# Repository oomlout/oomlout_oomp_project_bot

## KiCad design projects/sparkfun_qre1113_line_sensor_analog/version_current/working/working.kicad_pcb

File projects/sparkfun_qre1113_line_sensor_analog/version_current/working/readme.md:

# QRE1113_Line_Sensor-Analog by sparkfun  
This is a harvested standardized copy of a project from github.  
The original project can be found at:  
https://github.com/sparkfun/QRE1113_Line_Sensor-Analog  
Please consult that link for additional, details, files, and license information.  
Note: It was auto harvested and if the original repo had more than one board file or anything out of the ordinary the files here are likely not representative.

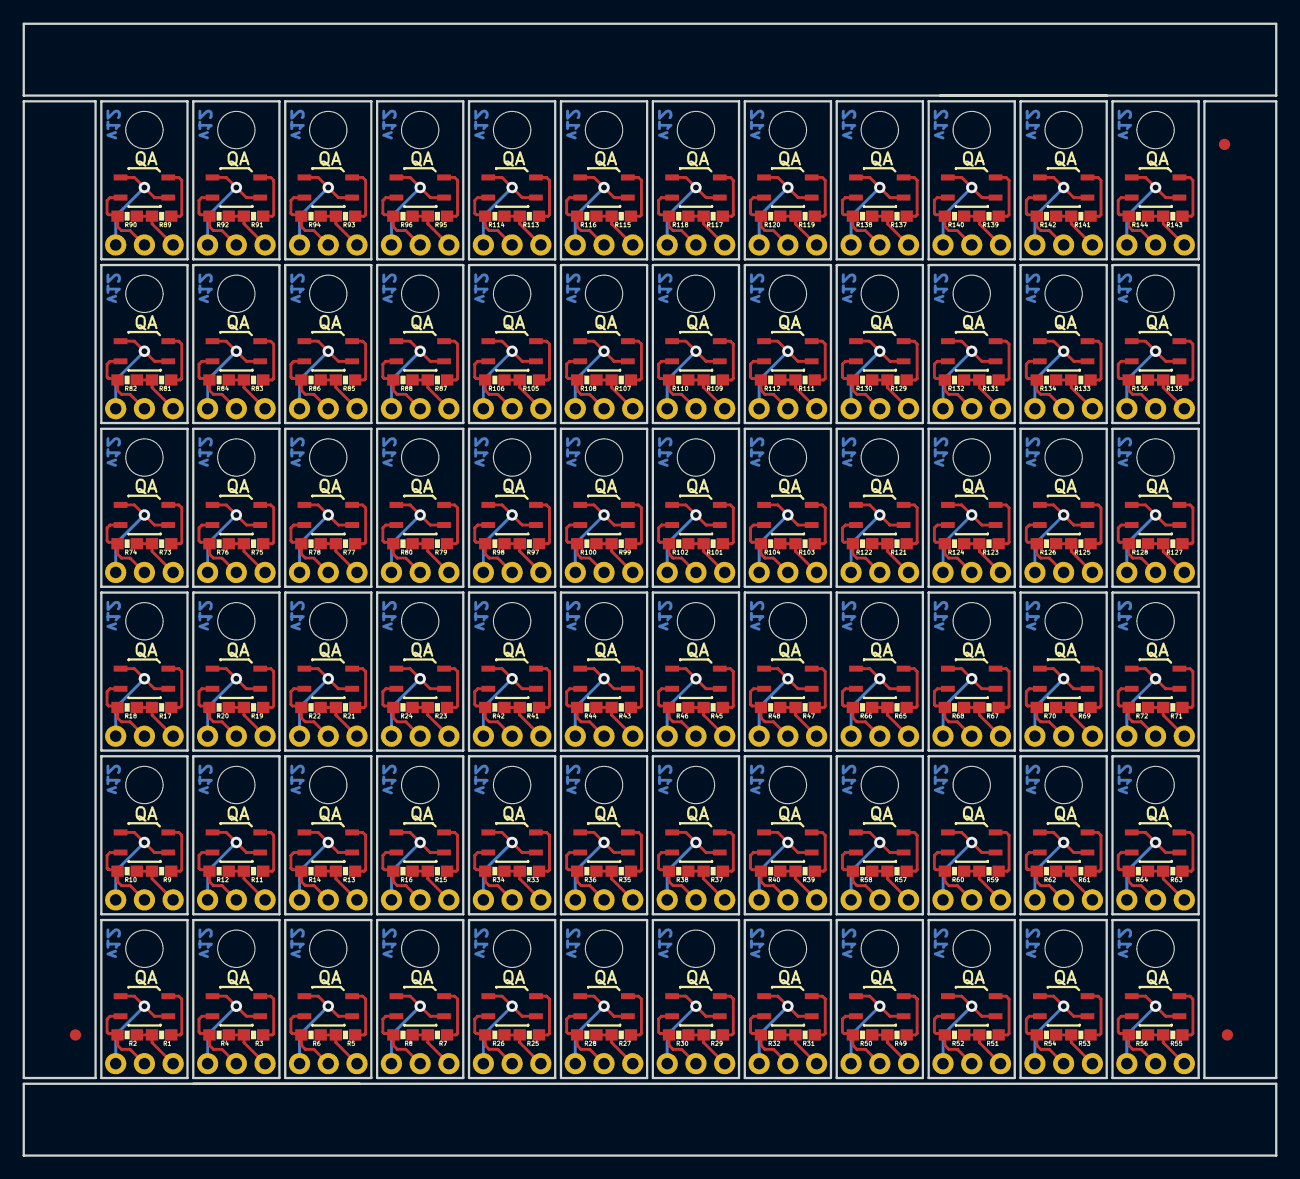
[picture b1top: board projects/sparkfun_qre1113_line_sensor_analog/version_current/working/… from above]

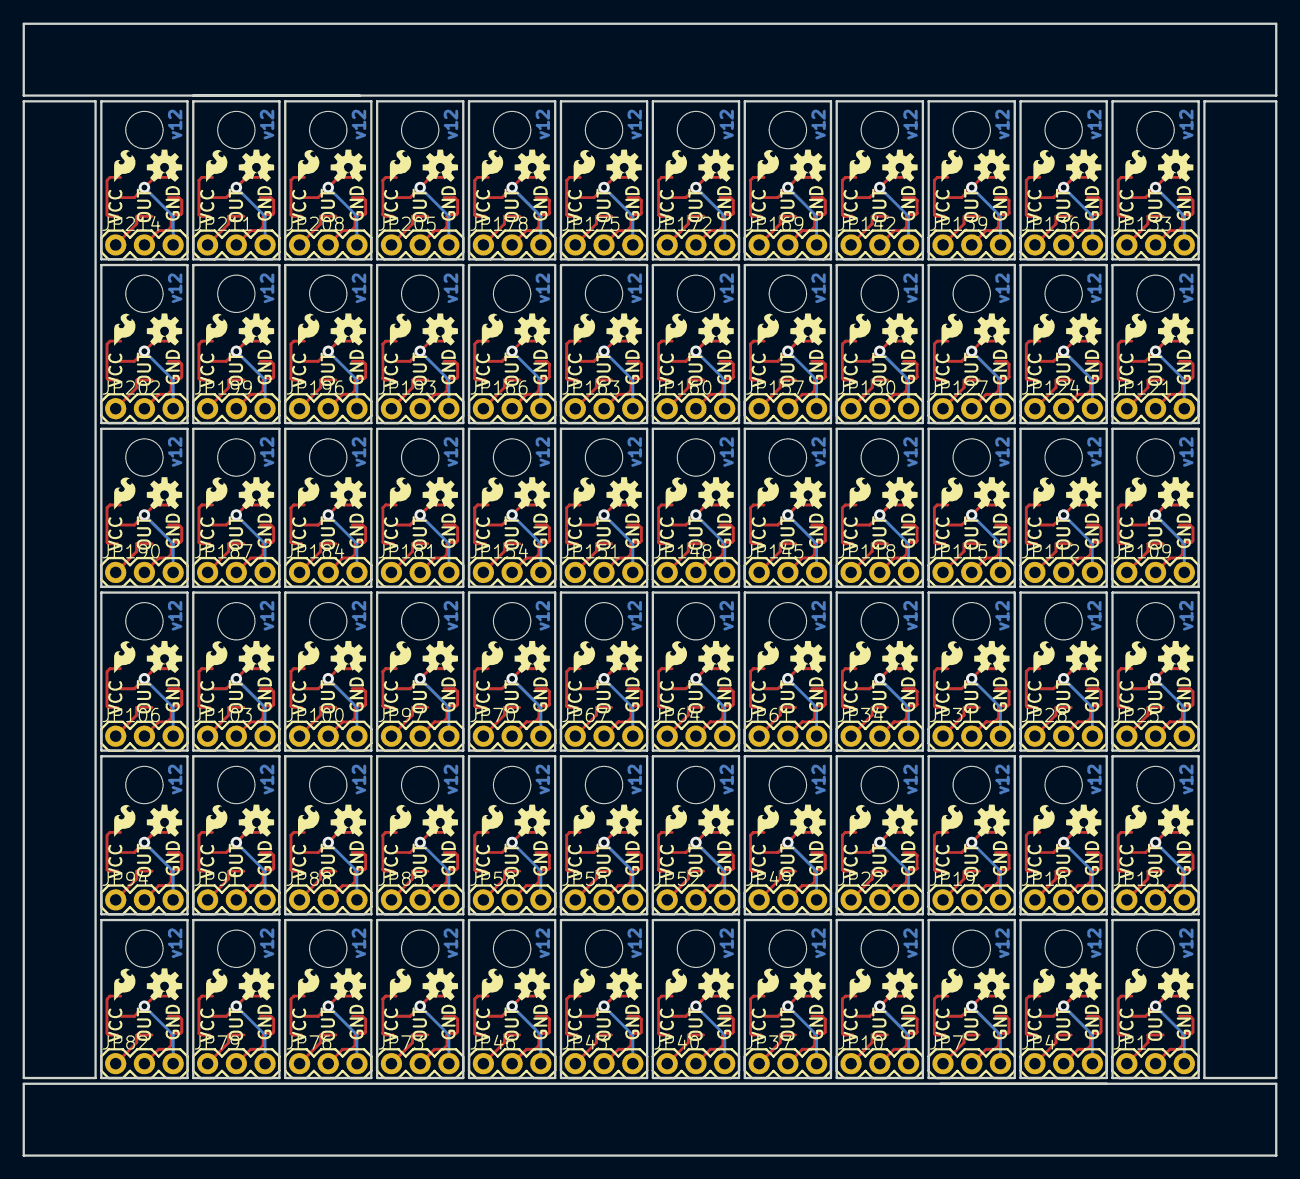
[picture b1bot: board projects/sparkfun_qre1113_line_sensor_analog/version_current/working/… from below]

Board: 2 copper layers, 110.7 x 100.1 mm, 507 parts (216 on the bottom side), 288 nets.

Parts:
E$1, E$4, E$5: FIDUCIAL-1X2
JP1, JP4, JP7, JP10, JP13, JP16, JP19, JP22, JP25, JP28, JP31, JP34, JP37, JP40, JP43, JP46, JP49, JP52, JP55, JP58, JP61, JP64, JP67, JP70, JP73, JP76, JP79, JP82, JP85, JP88, JP91, JP94, JP97, JP100, JP103, JP106, JP109, JP112, JP115, JP118, JP121, JP124, JP127, JP130, JP133, JP136, JP139, JP142, JP145, JP148, JP151, JP154, JP157, JP160, JP163, JP166, JP169, JP172, JP175, JP178, JP181, JP184, JP187, JP190, JP193, JP196, JP199, JP202, JP205, JP208, JP211, JP214: 1X03
JP2, JP5, JP8, JP11, JP14, JP17, JP20, JP23, JP26, JP29, JP32, JP35, JP38, JP41, JP44, JP47, JP50, JP53, JP56, JP59, JP62, JP65, JP68, JP71, JP74, JP77, JP80, JP83, JP86, JP89, JP92, JP95, JP98, JP101, JP104, JP107, JP110, JP113, JP116, JP119, JP122, JP125, JP128, JP131, JP134, JP137, JP140, JP143, JP146, JP149, JP152, JP155, JP158, JP161, JP164, JP167, JP170, JP173, JP176, JP179, JP182, JP185, JP188, JP191, JP194, JP197, JP200, JP203, JP206, JP209, JP212, JP215: LOGO-SFESK; SFE-LOGO-FLAME
JP3, JP6, JP9, JP12, JP15, JP18, JP21, JP24, JP27, JP30, JP33, JP36, JP39, JP42, JP45, JP48, JP51, JP54, JP57, JP60, JP63, JP66, JP69, JP72, JP75, JP78, JP81, JP84, JP87, JP90, JP93, JP96, JP99, JP102, JP105, JP108, JP111, JP114, JP117, JP120, JP123, JP126, JP129, JP132, JP135, JP138, JP141, JP144, JP147, JP150, JP153, JP156, JP159, JP162, JP165, JP168, JP171, JP174, JP177, JP180, JP183, JP186, JP189, JP192, JP195, JP198, JP201, JP204, JP207, JP210, JP213, JP216: STAND-OFF
R1, R3, R5, R7, R9, R11, R13, R15, R17, R19, R21, R23, R25, R27, R29, R31, R33, R35, R37, R39, R41, R43, R45, R47, R49, R51, R53, R55, R57, R59, R61, R63, R65, R67, R69, R71, R73, R75, R77, R79, R81, R83, R85, R87, R89, R91, R93, R95, R97, R99, R101, R103, R105, R107, R109, R111, R113, R115, R117, R119, R121, R123, R125, R127, R129, R131, R133, R135, R137, R139, R141, R143: 100; 0603-RES
R2, R4, R6, R8, R10, R12, R14, R16, R18, R20, R22, R24, R26, R28, R30, R32, R34, R36, R38, R40, R42, R44, R46, R48, R50, R52, R54, R56, R58, R60, R62, R64, R66, R68, R70, R72, R74, R76, R78, R80, R82, R84, R86, R88, R90, R92, R94, R96, R98, R100, R102, R104, R106, R108, R110, R112, R114, R116, R118, R120, R122, R124, R126, R128, R130, R132, R134, R136, R138, R140, R142, R144: 10K; 0603-RES
U1, U2, U3, U4, U5, U6, U7, U8, U9, U10, U11, U12, U13, U14, U15, U16, U17, U18, U19, U20, U21, U22, U23, U24, U25, U26, U27, U28, U29, U30, U31, U32, U33, U34, U35, U36, U37, U38, U39, U40, U41, U42, U43, U44, U45, U46, U47, U48, U49, U50, U51, U52, U53, U54, U55, U56, U57, U58, U59, U60, U61, U62, U63, U64, U65, U66, U67, U68, U69, U70, U71, U72: QRE11131:1; QRE1113-1_1
U$1, U$2, U$3, U$4, U$5, U$6, U$7, U$8, U$9, U$10, U$11, U$12, U$13, U$14, U$15, U$16, U$17, U$18, U$19, U$20, U$21, U$22, U$23, U$24, U$25, U$26, U$27, U$28, U$29, U$30, U$31, U$32, U$33, U$34, U$35, U$36, U$37, U$38, U$39, U$40, U$41, U$42, U$43, U$44, U$45, U$46, U$47, U$48, U$49, U$50, U$51, U$52, U$53, U$54, U$55, U$56, U$57, U$58, U$59, U$60, U$61, U$62, U$63, U$64, U$65, U$66, U$67, U$68, U$69, U$70, U$71, U$72: OSHW-LOGOS; OSHW-LOGO-S

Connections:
GND: JP1.3, U1.2, U1.4
GND1: JP4.3, U2.2, U2.4
GND2: JP7.3, U3.2, U3.4
GND3: JP10.3, U4.2, U4.4
GND4: JP13.3, U5.2, U5.4
GND5: JP16.3, U6.2, U6.4
GND6: JP19.3, U7.2, U7.4
GND7: JP22.3, U8.2, U8.4
GND8: JP25.3, U9.2, U9.4
GND9: JP28.3, U10.2, U10.4
GND10: JP31.3, U11.2, U11.4
GND11: JP34.3, U12.2, U12.4
GND12: JP37.3, U13.2, U13.4
GND13: JP40.3, U14.2, U14.4
GND14: JP43.3, U15.2, U15.4
GND15: JP46.3, U16.2, U16.4
GND16: JP49.3, U17.2, U17.4
GND17: JP52.3, U18.2, U18.4
GND18: JP55.3, U19.2, U19.4
GND19: JP58.3, U20.2, U20.4
GND20: JP61.3, U21.2, U21.4
GND21: JP64.3, U22.2, U22.4
GND22: JP67.3, U23.2, U23.4
GND23: JP70.3, U24.2, U24.4
GND24: JP73.3, U25.2, U25.4
GND25: JP76.3, U26.2, U26.4
GND26: JP79.3, U27.2, U27.4
GND27: JP82.3, U28.2, U28.4
GND28: JP85.3, U29.2, U29.4
GND29: JP88.3, U30.2, U30.4
GND30: JP91.3, U31.2, U31.4
GND31: JP94.3, U32.2, U32.4
GND32: JP97.3, U33.2, U33.4
GND33: JP100.3, U34.2, U34.4
GND34: JP103.3, U35.2, U35.4
GND35: JP106.3, U36.2, U36.4
GND36: JP109.3, U37.2, U37.4
GND37: JP112.3, U38.2, U38.4
GND38: JP115.3, U39.2, U39.4
GND39: JP118.3, U40.2, U40.4
GND40: JP121.3, U41.2, U41.4
GND41: JP124.3, U42.2, U42.4
GND42: JP127.3, U43.2, U43.4
GND43: JP130.3, U44.2, U44.4
GND44: JP133.3, U45.2, U45.4
GND45: JP136.3, U46.2, U46.4
GND46: JP139.3, U47.2, U47.4
GND47: JP142.3, U48.2, U48.4
GND48: JP145.3, U49.2, U49.4
GND49: JP148.3, U50.2, U50.4
GND50: JP151.3, U51.2, U51.4
GND51: JP154.3, U52.2, U52.4
GND52: JP157.3, U53.2, U53.4
GND53: JP160.3, U54.2, U54.4
GND54: JP163.3, U55.2, U55.4
GND55: JP166.3, U56.2, U56.4
GND56: JP169.3, U57.2, U57.4
GND57: JP172.3, U58.2, U58.4
GND58: JP175.3, U59.2, U59.4
GND59: JP178.3, U60.2, U60.4
GND60: JP181.3, U61.2, U61.4
GND61: JP184.3, U62.2, U62.4
GND62: JP187.3, U63.2, U63.4
GND63: JP190.3, U64.2, U64.4
GND64: JP193.3, U65.2, U65.4
GND65: JP196.3, U66.2, U66.4
GND66: JP199.3, U67.2, U67.4
GND67: JP202.3, U68.2, U68.4
GND68: JP205.3, U69.2, U69.4
GND69: JP208.3, U70.2, U70.4
GND70: JP211.3, U71.2, U71.4
GND71: JP214.3, U72.2, U72.4
unnamed: R1.1, U1.1
unnamed: R3.1, U2.1
unnamed: R5.1, U3.1
unnamed: R7.1, U4.1
unnamed: R9.1, U5.1
unnamed: R11.1, U6.1
unnamed: R13.1, U7.1
unnamed: R15.1, U8.1
unnamed: R17.1, U9.1
unnamed: R19.1, U10.1
unnamed: R21.1, U11.1
unnamed: R23.1, U12.1
unnamed: R25.1, U13.1
unnamed: R27.1, U14.1
unnamed: R29.1, U15.1
unnamed: R31.1, U16.1
unnamed: R33.1, U17.1
unnamed: R35.1, U18.1
unnamed: R37.1, U19.1
unnamed: R39.1, U20.1
unnamed: R41.1, U21.1
unnamed: R43.1, U22.1
unnamed: R45.1, U23.1
unnamed: R47.1, U24.1
unnamed: R49.1, U25.1
unnamed: R51.1, U26.1
unnamed: R53.1, U27.1
unnamed: R55.1, U28.1
unnamed: R57.1, U29.1
unnamed: R59.1, U30.1
unnamed: R61.1, U31.1
unnamed: R63.1, U32.1
unnamed: R65.1, U33.1
unnamed: R67.1, U34.1
unnamed: R69.1, U35.1
unnamed: R71.1, U36.1
unnamed: R73.1, U37.1
unnamed: R75.1, U38.1
unnamed: R77.1, U39.1
unnamed: R79.1, U40.1
unnamed: R81.1, U41.1
unnamed: R83.1, U42.1
unnamed: R85.1, U43.1
unnamed: R87.1, U44.1
unnamed: R89.1, U45.1
unnamed: R91.1, U46.1
unnamed: R93.1, U47.1
unnamed: R95.1, U48.1
unnamed: R97.1, U49.1
unnamed: R99.1, U50.1
unnamed: R101.1, U51.1
unnamed: R103.1, U52.1
unnamed: R105.1, U53.1
unnamed: R107.1, U54.1
unnamed: R109.1, U55.1
unnamed: R111.1, U56.1
unnamed: R113.1, U57.1
unnamed: R115.1, U58.1
unnamed: R117.1, U59.1
unnamed: R119.1, U60.1
unnamed: R121.1, U61.1
unnamed: R123.1, U62.1
unnamed: R125.1, U63.1
unnamed: R127.1, U64.1
unnamed: R129.1, U65.1
unnamed: R131.1, U66.1
unnamed: R133.1, U67.1
unnamed: R135.1, U68.1
unnamed: R137.1, U69.1
unnamed: R139.1, U70.1
unnamed: R141.1, U71.1
unnamed: R143.1, U72.1
OUT: JP1.2, R2.2, U1.3
OUT1: JP4.2, R4.2, U2.3
OUT2: JP7.2, R6.2, U3.3
OUT3: JP10.2, R8.2, U4.3
OUT4: JP13.2, R10.2, U5.3
OUT5: JP16.2, R12.2, U6.3
OUT6: JP19.2, R14.2, U7.3
OUT7: JP22.2, R16.2, U8.3
OUT8: JP25.2, R18.2, U9.3
OUT9: JP28.2, R20.2, U10.3
OUT10: JP31.2, R22.2, U11.3
OUT11: JP34.2, R24.2, U12.3
OUT12: JP37.2, R26.2, U13.3
OUT13: JP40.2, R28.2, U14.3
OUT14: JP43.2, R30.2, U15.3
OUT15: JP46.2, R32.2, U16.3
OUT16: JP49.2, R34.2, U17.3
OUT17: JP52.2, R36.2, U18.3
OUT18: JP55.2, R38.2, U19.3
OUT19: JP58.2, R40.2, U20.3
OUT20: JP61.2, R42.2, U21.3
OUT21: JP64.2, R44.2, U22.3
OUT22: JP67.2, R46.2, U23.3
OUT23: JP70.2, R48.2, U24.3
OUT24: JP73.2, R50.2, U25.3
OUT25: JP76.2, R52.2, U26.3
OUT26: JP79.2, R54.2, U27.3
OUT27: JP82.2, R56.2, U28.3
OUT28: JP85.2, R58.2, U29.3
OUT29: JP88.2, R60.2, U30.3
OUT30: JP91.2, R62.2, U31.3
OUT31: JP94.2, R64.2, U32.3
OUT32: JP97.2, R66.2, U33.3
OUT33: JP100.2, R68.2, U34.3
OUT34: JP103.2, R70.2, U35.3
OUT35: JP106.2, R72.2, U36.3
OUT36: JP109.2, R74.2, U37.3
OUT37: JP112.2, R76.2, U38.3
OUT38: JP115.2, R78.2, U39.3
OUT39: JP118.2, R80.2, U40.3
OUT40: JP121.2, R82.2, U41.3
OUT41: JP124.2, R84.2, U42.3
OUT42: JP127.2, R86.2, U43.3
OUT43: JP130.2, R88.2, U44.3
OUT44: JP133.2, R90.2, U45.3
OUT45: JP136.2, R92.2, U46.3
OUT46: JP139.2, R94.2, U47.3
OUT47: JP142.2, R96.2, U48.3
OUT48: JP145.2, R98.2, U49.3
OUT49: JP148.2, R100.2, U50.3
OUT50: JP151.2, R102.2, U51.3
OUT51: JP154.2, R104.2, U52.3
OUT52: JP157.2, R106.2, U53.3
OUT53: JP160.2, R108.2, U54.3
OUT54: JP163.2, R110.2, U55.3
OUT55: JP166.2, R112.2, U56.3
OUT56: JP169.2, R114.2, U57.3
OUT57: JP172.2, R116.2, U58.3
OUT58: JP175.2, R118.2, U59.3
OUT59: JP178.2, R120.2, U60.3
OUT60: JP181.2, R122.2, U61.3
OUT61: JP184.2, R124.2, U62.3
OUT62: JP187.2, R126.2, U63.3
OUT63: JP190.2, R128.2, U64.3
OUT64: JP193.2, R130.2, U65.3
OUT65: JP196.2, R132.2, U66.3
OUT66: JP199.2, R134.2, U67.3
OUT67: JP202.2, R136.2, U68.3
OUT68: JP205.2, R138.2, U69.3
OUT69: JP208.2, R140.2, U70.3
OUT70: JP211.2, R142.2, U71.3
OUT71: JP214.2, R144.2, U72.3
VCC: JP1.1, R1.2, R2.1
VCC1: JP4.1, R3.2, R4.1
VCC2: JP7.1, R5.2, R6.1
VCC3: JP10.1, R7.2, R8.1
VCC4: JP13.1, R9.2, R10.1
VCC5: JP16.1, R11.2, R12.1
VCC6: JP19.1, R13.2, R14.1
VCC7: JP22.1, R15.2, R16.1
VCC8: JP25.1, R17.2, R18.1
VCC9: JP28.1, R19.2, R20.1
VCC10: JP31.1, R21.2, R22.1
VCC11: JP34.1, R23.2, R24.1
VCC12: JP37.1, R25.2, R26.1
VCC13: JP40.1, R27.2, R28.1
VCC14: JP43.1, R29.2, R30.1
VCC15: JP46.1, R31.2, R32.1
VCC16: JP49.1, R33.2, R34.1
VCC17: JP52.1, R35.2, R36.1
VCC18: JP55.1, R37.2, R38.1
VCC19: JP58.1, R39.2, R40.1
VCC20: JP61.1, R41.2, R42.1
VCC21: JP64.1, R43.2, R44.1
VCC22: JP67.1, R45.2, R46.1
VCC23: JP70.1, R47.2, R48.1
VCC24: JP73.1, R49.2, R50.1
VCC25: JP76.1, R51.2, R52.1
VCC26: JP79.1, R53.2, R54.1
VCC27: JP82.1, R55.2, R56.1
VCC28: JP85.1, R57.2, R58.1
VCC29: JP88.1, R59.2, R60.1
VCC30: JP91.1, R61.2, R62.1
VCC31: JP94.1, R63.2, R64.1
VCC32: JP97.1, R65.2, R66.1
VCC33: JP100.1, R67.2, R68.1
VCC34: JP103.1, R69.2, R70.1
VCC35: JP106.1, R71.2, R72.1
VCC36: JP109.1, R73.2, R74.1
VCC37: JP112.1, R75.2, R76.1
VCC38: JP115.1, R77.2, R78.1
VCC39: JP118.1, R79.2, R80.1
VCC40: JP121.1, R81.2, R82.1
VCC41: JP124.1, R83.2, R84.1
VCC42: JP127.1, R85.2, R86.1
VCC43: JP130.1, R87.2, R88.1
VCC44: JP133.1, R89.2, R90.1
VCC45: JP136.1, R91.2, R92.1
VCC46: JP139.1, R93.2, R94.1
VCC47: JP142.1, R95.2, R96.1
VCC48: JP145.1, R97.2, R98.1
VCC49: JP148.1, R99.2, R100.1
VCC50: JP151.1, R101.2, R102.1
VCC51: JP154.1, R103.2, R104.1
VCC52: JP157.1, R105.2, R106.1
VCC53: JP160.1, R107.2, R108.1
VCC54: JP163.1, R109.2, R110.1
VCC55: JP166.1, R111.2, R112.1
VCC56: JP169.1, R113.2, R114.1
VCC57: JP172.1, R115.2, R116.1
VCC58: JP175.1, R117.2, R118.1
VCC59: JP178.1, R119.2, R120.1
VCC60: JP181.1, R121.2, R122.1
VCC61: JP184.1, R123.2, R124.1
VCC62: JP187.1, R125.2, R126.1
VCC63: JP190.1, R127.2, R128.1
VCC64: JP193.1, R129.2, R130.1
VCC65: JP196.1, R131.2, R132.1
VCC66: JP199.1, R133.2, R134.1
VCC67: JP202.1, R135.2, R136.1
VCC68: JP205.1, R137.2, R138.1
VCC69: JP208.1, R139.2, R140.1
VCC70: JP211.1, R141.2, R142.1
VCC71: JP214.1, R143.2, R144.1

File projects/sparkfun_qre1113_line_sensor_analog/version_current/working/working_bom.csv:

Row,Description,Part,References,Value,Footprint,Quantity Per PCB,Status,Datasheet
1,,CREATIVE_COMMONS,CC_TEXT1,CREATIVE_COMMONS,CREATIVE_COMMONS,1, ,
2,,LOGO-SFESK,JP2,LOGO-SFESK,SFE-LOGO-FLAME,1, ,
3,,M03PTH,JP1,M03PTH,1X03,1, ,
4,,STAND-OFF,JP3,STAND-OFF,STAND-OFF,1, ,
5,,RESISTOR0603-RES,R1,100,0603-RES,1, ,
6,,RESISTOR0603-RES,R2,10K,0603-RES,1, ,
7,,QRE11131{colon}1,U1,QRE11131{colon}1,QRE1113-1_1,1, ,
8,,OSHW-LOGOS,U$1,OSHW-LOGOS,OSHW-LOGO-S,1, ,





Project info:
Schematic:,working
Variant:,default
Revision:,
Date:,2023-08-06_12-56-13
KiCad Version:,7.0.6-7.0.6~ubuntu22.04.1
Statistics:
Component Groups:,8
Component Count:,8 (0 SMD/ 0 THT)
Fitted Components:,8 (0 SMD/ 0 THT)
Number of PCBs:,1
Total Components:,8

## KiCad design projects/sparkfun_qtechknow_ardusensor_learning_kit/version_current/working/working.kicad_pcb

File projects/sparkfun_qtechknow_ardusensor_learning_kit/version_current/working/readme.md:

# OOMP Project  
## Qtechknow_ArduSensor_Learning_Kit  by sparkfun  
  
oomp key: oomp_projects_flat_sparkfun_qtechknow_ardusensor_learning_kit  
(snippet of original readme)  
  
Qtechknow ArduSensor Learning Kit  
=================================  
  
[  
*Qtechknow ArduSensor Learning Kit(11470)*](https://www.sparkfun.com/products/11470)  

Repository Contents  
-------------------  
  
* **/ArduSensor PCB** - All  design files for the ArduSensor PCB.   
* **/ArduSensor Shield** - All design files for the ArduSensor Shield that is Uno-footprint compatible.   

License Information  
-------------------  
The hardware is released under [Creative Commons ShareAlike 4.0 International](https://creativecommons.org/licenses/by-sa/4.0/).  

->This product is a collaboration with Quin at Qtechknow.com.   
You can find additional resources on these products [here](http://learn.qtechknow.com/)<-  
  full source readme at [readme_src.md](readme_src.md)  
  
source repo at: [https://github.com/sparkfun/Qtechknow_ArduSensor_Learning_Kit](https://github.com/sparkfun/Qtechknow_ArduSensor_Learning_Kit)  
## Board  

## Schematic  

[schematic pdf](working_schematic.pdf)  
## Images

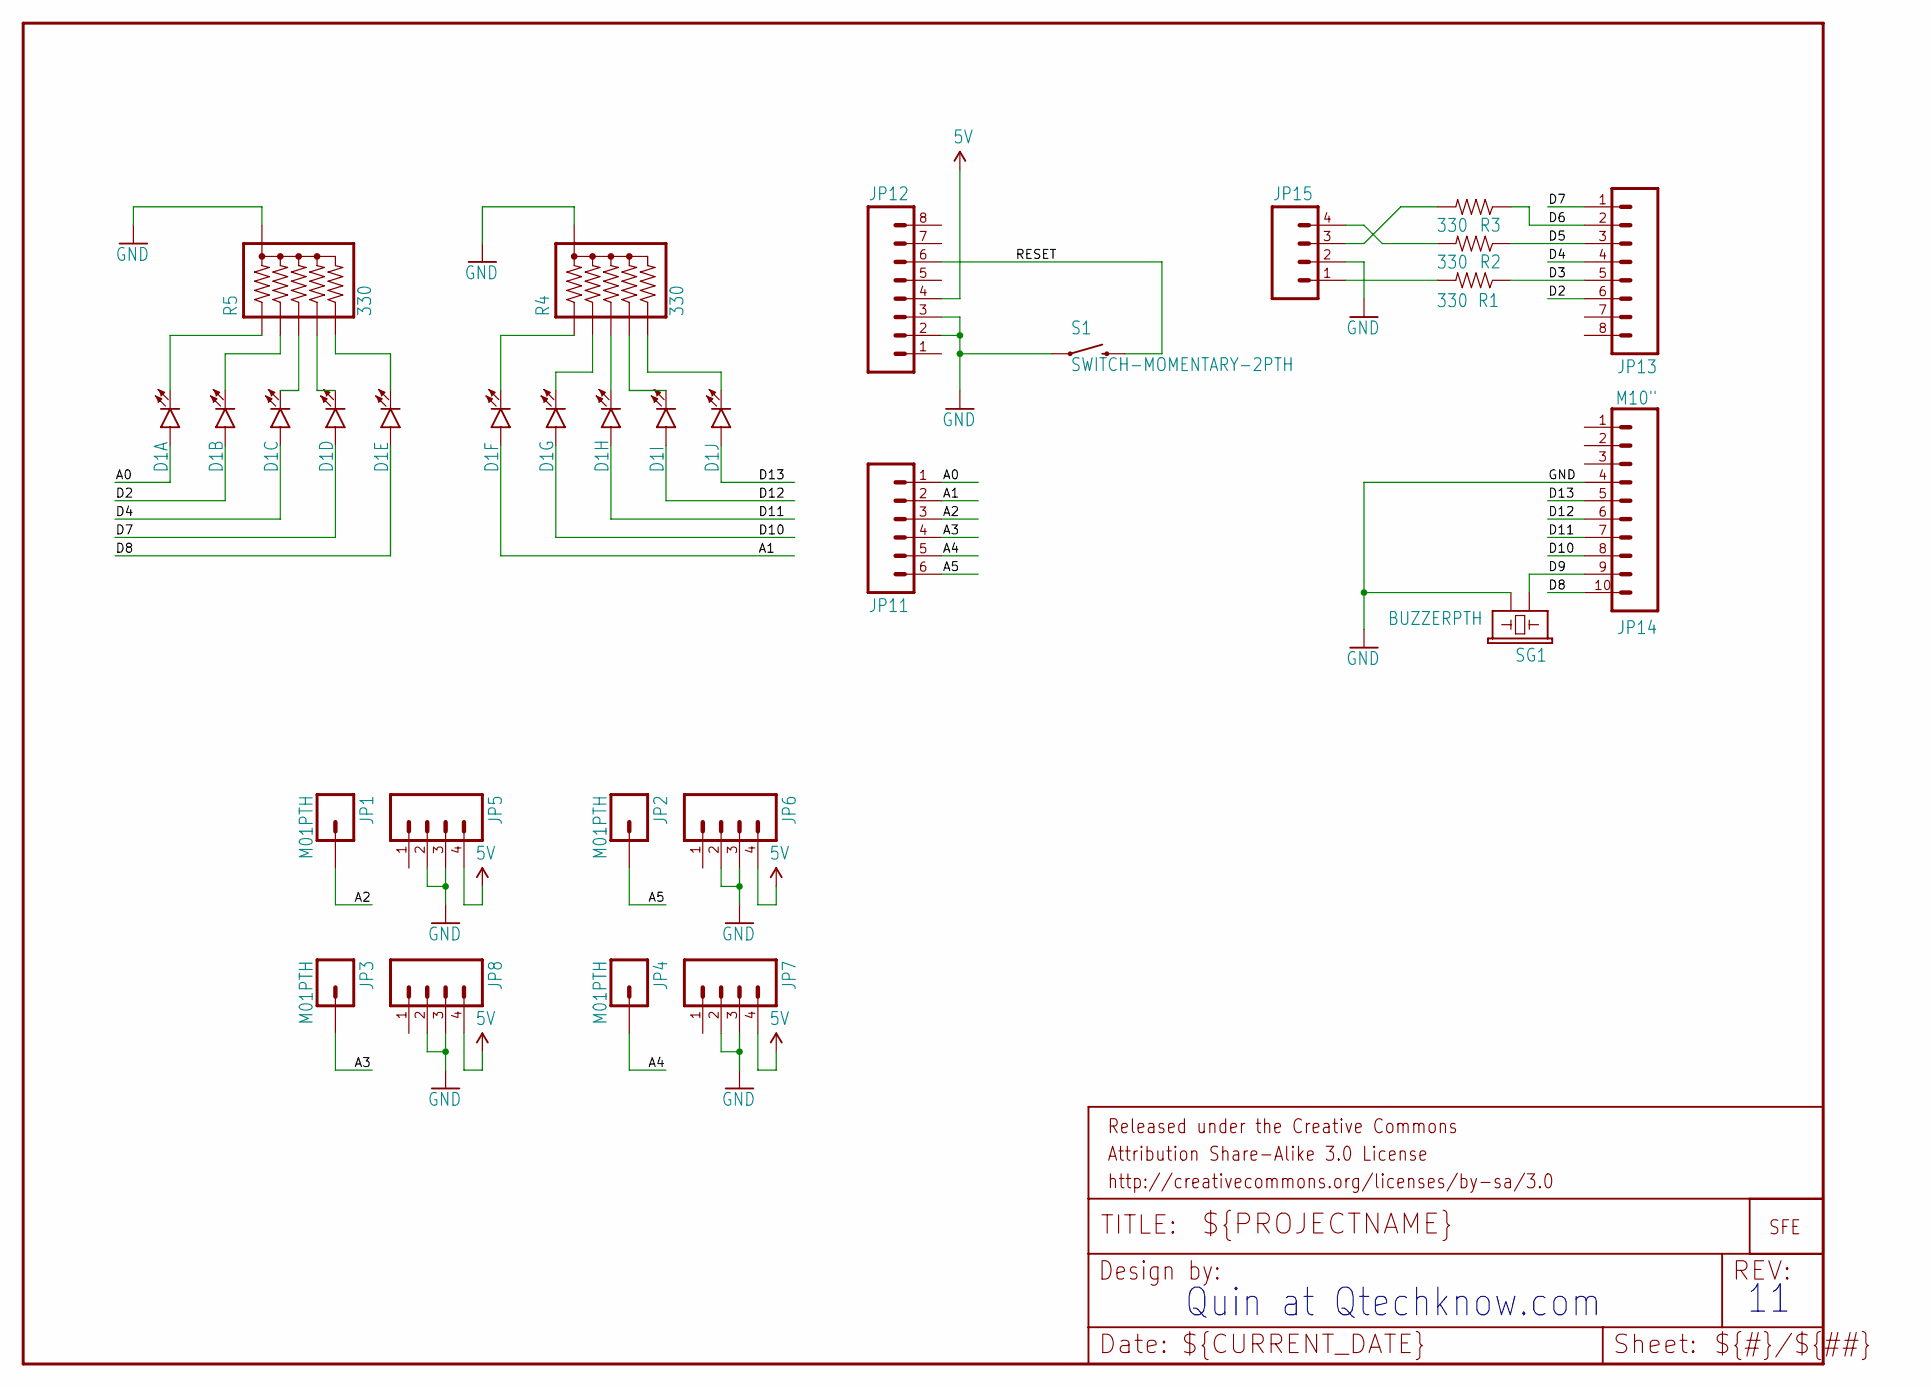
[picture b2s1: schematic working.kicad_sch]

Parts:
D1: LED_BARGRAPH_10; LED_BARGAPH_10
FRAME1: FRAME-LETTER; CREATIVE_COMMONS
JP1, JP2, JP3, JP4: M01PTH; 1X01
JP5, JP6, JP7, JP8, JP15: M04PTH; 1X04
JP9: LOGO-SFENEW; SFE-NEW-WEBLOGO
JP11: M06SIP; 1X06
JP12, JP13: M081X08; 1X08
JP14: M10"; 1X10
R1, R2, R3: 330; 1_6W-RES
R4, R5: 330; RPACK-SIP-PTH-5
S1: SWITCH-MOMENTARY-2PTH; TACTILE-PTH
SG1: BUZZERPTH; BUZZER-12MM

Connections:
5V: JP5.4, JP6.4, JP7.4, JP8.4, JP12.4
A0: D1.1 (A), JP11.1
A1: D1.6 (A), JP11.2
A2: JP1.1, JP11.3
A3: JP3.1, JP11.4
A4: JP4.1, JP11.5
A5: JP2.1, JP11.6
D2: D1.2 (A), JP13.6
D3: JP13.5, R1.1
D4: D1.3 (A), JP13.4
D5: JP13.3, R2.1
D6: JP13.2, R3.1
D7: D1.4 (A), JP13.1
D8: D1.5 (A), JP14.10
D9: JP14.9, SG1.+ (1)
D10: D1.7 (A), JP14.8
D11: D1.8 (A), JP14.7
D12: D1.9 (A), JP14.6
D13: D1.10 (A), JP14.5
GND: JP5.2, JP5.3, JP6.2, JP6.3, JP7.2, JP7.3, JP8.2, JP8.3, JP12.2, JP12.3, JP14.4, JP15.2, R4.P$1 (1), R5.P$1 (1), S1.1, SG1.- (2)
unnamed: JP15.1, R1.2
unnamed: JP15.4, R2.2
unnamed: D1.11 (C), R4.P$6 (6)
unnamed: D1.12 (C), R4.P$5 (5)
unnamed: D1.13 (C), R4.P$4 (4)
unnamed: D1.14 (C), R4.P$3 (3)
unnamed: D1.15 (C), R4.P$2 (2)
unnamed: D1.16 (C), R5.P$6 (6)
unnamed: D1.17 (C), R5.P$5 (5)
unnamed: D1.18 (C), R5.P$4 (4)
unnamed: D1.19 (C), R5.P$3 (3)
unnamed: D1.20 (C), R5.P$2 (2)
unnamed: JP15.3, R3.2
RESET: JP12.6, S1.3 (2)

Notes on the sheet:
Quin at Qtechknow.com

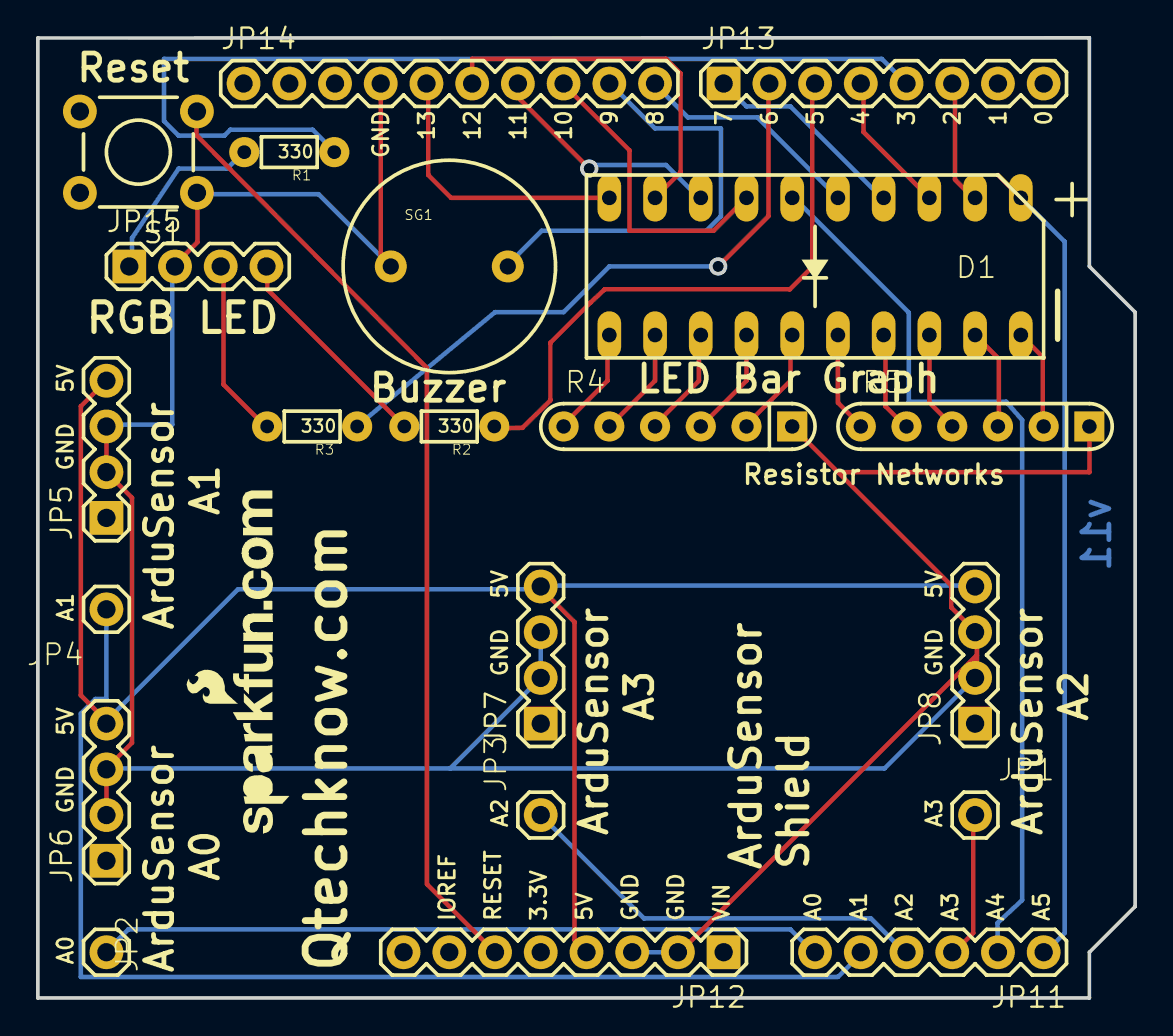
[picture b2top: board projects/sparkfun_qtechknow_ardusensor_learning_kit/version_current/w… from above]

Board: 4 copper layers, 61.0 x 53.3 mm, 23 parts (0 on the bottom side), 34 nets.

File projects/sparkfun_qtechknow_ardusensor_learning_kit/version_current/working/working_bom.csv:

Row,Description,Part,References,Value,Footprint,Quantity Per PCB,Status,Datasheet
1,,LED_BARGRAPH_10,D1,LED_BARGRAPH_10,LED_BARGAPH_10,1, ,
2,,FRAME-LETTER,FRAME1,FRAME-LETTER,CREATIVE_COMMONS,1, ,
3,,LOGO-SFENEW,JP9,LOGO-SFENEW,SFE-NEW-WEBLOGO,1, ,
4,,M01PTH,JP1 JP2 JP3 JP4,M01PTH,1X01,4, ,
5,,M04PTH,JP5 JP6 JP7 JP8 JP15,M04PTH,1X04,5, ,
6,,M06SIP,JP11,M06SIP,1X06,1, ,
7,,M081X08,JP12 JP13,M081X08,1X08,2, ,
8,,M10{dblquote},JP14,M10{dblquote},1X10,1, ,
9,,RESISTORPTH-1/6W,R1 R2 R3,330,1_6W-RES,3, ,
10,,RPACK-BUSSED-SIP-PTH-5,R4 R5,330,RPACK-SIP-PTH-5,2, ,
11,,SWITCH-MOMENTARY-2PTH,S1,SWITCH-MOMENTARY-2PTH,TACTILE-PTH,1, ,
12,,BUZZERPTH,SG1,BUZZERPTH,BUZZER-12MM,1, ,





Project info:
Schematic:,working
Variant:,default
Revision:,
Date:,2023-08-06_12-56-13
KiCad Version:,7.0.6-7.0.6~ubuntu22.04.1
Statistics:
Component Groups:,12
Component Count:,23 (0 SMD/ 0 THT)
Fitted Components:,23 (0 SMD/ 0 THT)
Number of PCBs:,1
Total Components:,23

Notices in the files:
projects/sparkfun_qre1113_line_sensor_analog/version_current/working/working.kicad_sch:
http://creativecommons.org/licenses/by-sa/3.0
Released under the Creative Commons Attribution Share-Alike 3.0 License
parts and their libraries:
Released under the Creative Commons Attribution Share-Alike 4.0 License
